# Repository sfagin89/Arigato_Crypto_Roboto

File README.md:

# Arigato the Crypto Roboto

EC544 Networking the Physical World

Spring 2022 Final Project

This project deploys a Raspberry Pi robotic car, whose movements are controlled by payments to a crypto-wallet. The robot is subscribed to a movement command topic on an AWS MQTT server. Messages are published to that topic when the robot’s crypto-wallet receives currency, Dogecoin in this case. A user scans a QR code that appears on an e-ink display sitting on top of the robot. The display is controlled by a FRDM-64F board and it interfaces with the board via a custom PCB.

Our project employs various technologies, including low-level firmware, custom PCB design, IoT communication, APIs, and crypto-currency. Ian Chadwick connected the robot with MQTT, Sara Fagin created the custom PCB for the e-ink display, and Santiago Gomez developed the e-ink firmware for the FRDM-K64F board. He is also responsible for the client application that links the robot’s crypto-wallet with its MQTT Message Broker. This report delves into the implementation of each component. Furthermore, each component discussion provides insight into the development of the respective engineer.

## Hardware
- [NXP FRDM-K64F Development Board](https://www.nxp.com/design/development-boards/freedom-development-boards/mcu-boards/freedom-development-platform-for-kinetis-k64-k63-and-k24-mcus:FRDM-K64F)
- [Waveshare’s 2.9 inch V2 e-ink display](https://www.waveshare.com/wiki/4.2inch_e-Paper_Module)
- [Adafruit Stepper + DC Motor FeatherWing motor control board](https://learn.adafruit.com/adafruit-stepper-dc-motor-featherwing)
- [RaspberryPi 3 B+](https://www.raspberrypi.com/products/raspberry-pi-3-model-b-plus/)
- [JetBot Chassis and motors](https://jetbot.org/master/index.html)
- [Custom PCB for e-Ink](https://github.com/sfagin89/Arigato_Crypto_Roboto/tree/main/PCB_files)
  - [Documentation of Full PCB Assembly](https://github.com/sfagin89/Arigato_Crypto_Roboto/tree/main/PCB_files/PCB%20Assembly)

## Software
- [Custom e-Ink Firmware](https://github.com/sfagin89/Arigato_Crypto_Roboto/tree/main/eink_firmware/development/eink_spi_firmware)
- [Robot Software](https://github.com/sfagin89/Arigato_Crypto_Roboto/tree/main/RPi)
- [Crypto App](https://github.com/sfagin89/Arigato_Crypto_Roboto/tree/main/crypto_app)

## Implementation Video
- [EC544 - Arigato Crypto Roboto](https://www.youtube.com/watch?v=zG-Wq4VXOKg)

## Final Report
- [Final Report](https://github.com/sfagin89/Arigato_Crypto_Roboto/blob/main/Final%20Project%20Report.pdf)

## Custom PCB Schematic and Board Layout

### Final PCB Schematic

### Final PCB Board Layout

### PCB Board Top Layer

### PCB Board Bottom Layer

## Functional Block Diagrams

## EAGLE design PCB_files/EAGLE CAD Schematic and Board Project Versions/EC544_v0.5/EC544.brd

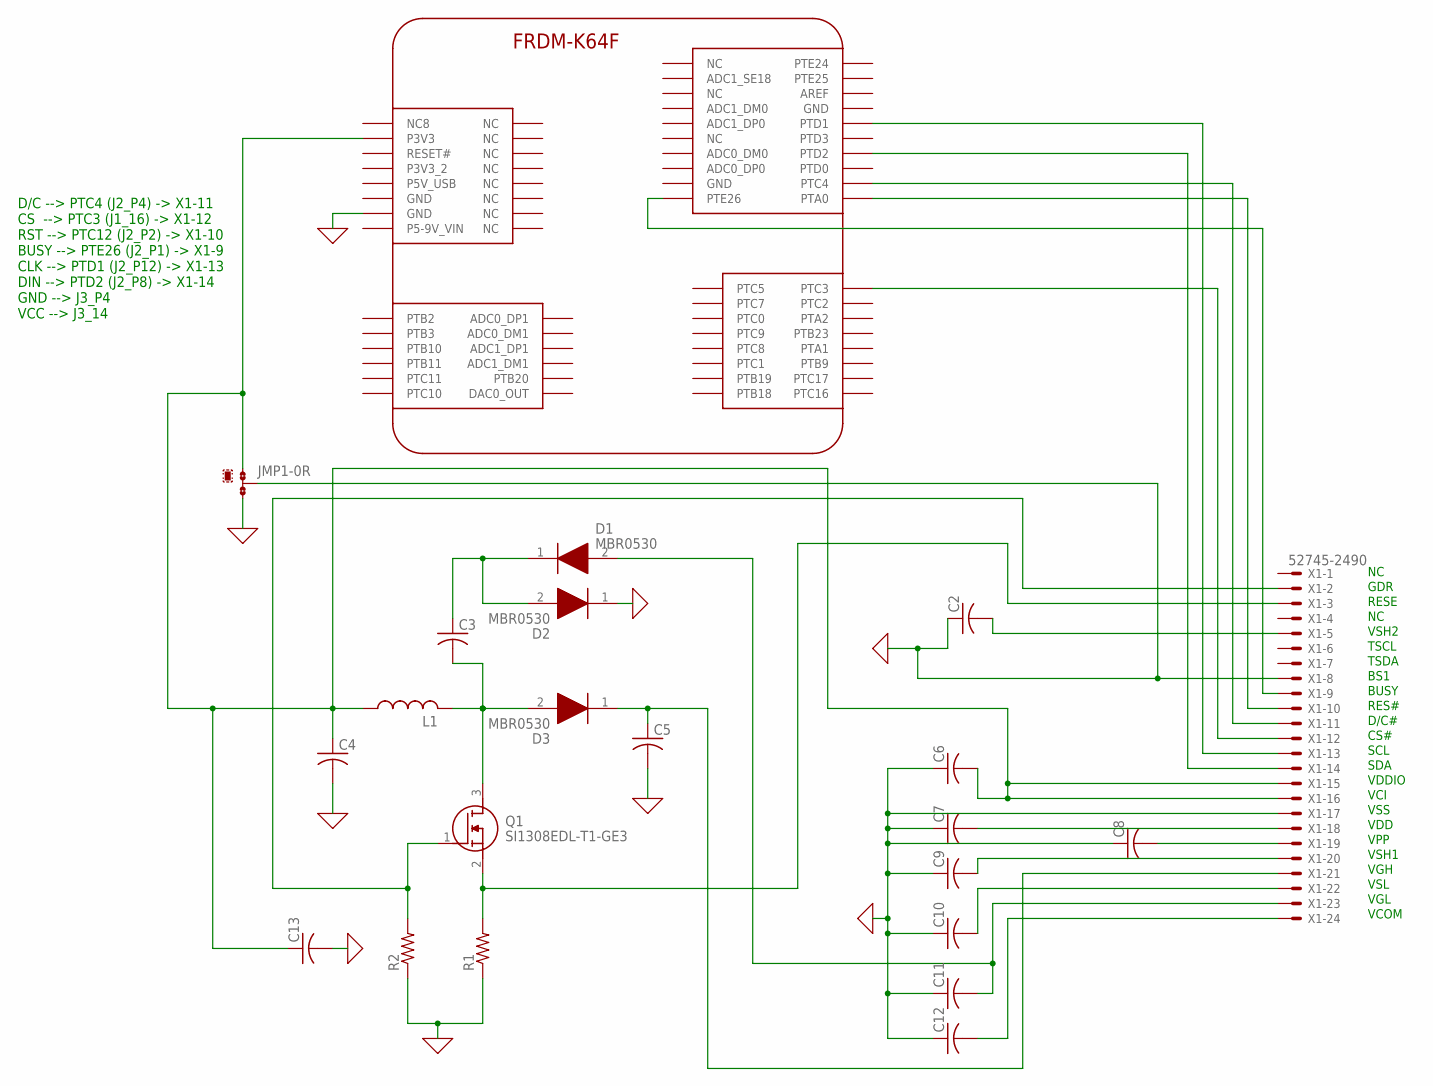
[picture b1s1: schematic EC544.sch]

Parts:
C2, C3, C4, C5, C6, C7, C8, C9, C10, C11, C12, C13: C-US025-024X044; C025-024X044
D1, D2, D3: MBR0530; SOD3716X135N
FRDM1: FRDM-K64FNORMAL; FRDM_K64F
JMP1: 0R-JUMPA; A0R-JMP
L1: L-USPIS2816; PIS2816
Q1: SI1308EDL-T1-GE3; SOT65P210X110-3N
R1, R2: R-US_0204/5; 0204/5
X1: 52745-2490

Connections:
0: C2.1, C4.2, C5.2, C6.1, C7.1, C8.1, C9.1, C10.1, C11.1, C12.1, C13.2, D2.1 (K), FRDM1.J3.14 (GND), JMP1.2, JMP1.3, R1.1, R2.1, X1.8, X1.17
unnamed: C2.2, X1.5
unnamed: C3.1, D1.1 (K), D2.2 (A)
unnamed: C7.2, X1.18
unnamed: C9.2, X1.20
unnamed: C10.2, X1.22
unnamed: C11.2, D1.2 (A), X1.23
unnamed: C12.2, X1.24
unnamed: C3.2, D3.2 (A), L1.2, Q1.3 (D)
unnamed: C5.1, D3.1 (K), X1.21
unnamed: Q1.1 (G), R2.2, X1.2
unnamed: Q1.2 (S), R1.2, X1.3
unnamed: FRDM1.J2.1 (PTE26), X1.9
unnamed: FRDM1.J2.2 (PTA0), X1.10
unnamed: FRDM1.J2.4 (PTC4), X1.11
unnamed: FRDM1.J1.16 (PTC3), X1.12
unnamed: FRDM1.J2.12 (PTD1), X1.13
unnamed: FRDM1.J2.8 (PTD2), X1.14
unnamed: C8.2, X1.19

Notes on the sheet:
D/C --> PTC4 (J2_P4) -> X1-11 CS --> PTC3 (J1_16) -> X1-12 RST --> PTC12 (J2_P2) -> X1-10 BUSY --> PTE26 (J2_P1) -> X1-9 CLK --> PTD1 (J2_P12) -> X1-13 DIN --> PTD2 (J2_P8) -> X1-14 GND --> J3_P4 VCC --> J3_14
NC GDR RESE NC VSH2 TSCL TSDA BS1 BUSY RES# D/C# CS# SCL SDA VDDIO VCI VSS VDD VPP VSH1 VGH VSL VGL VCOM

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
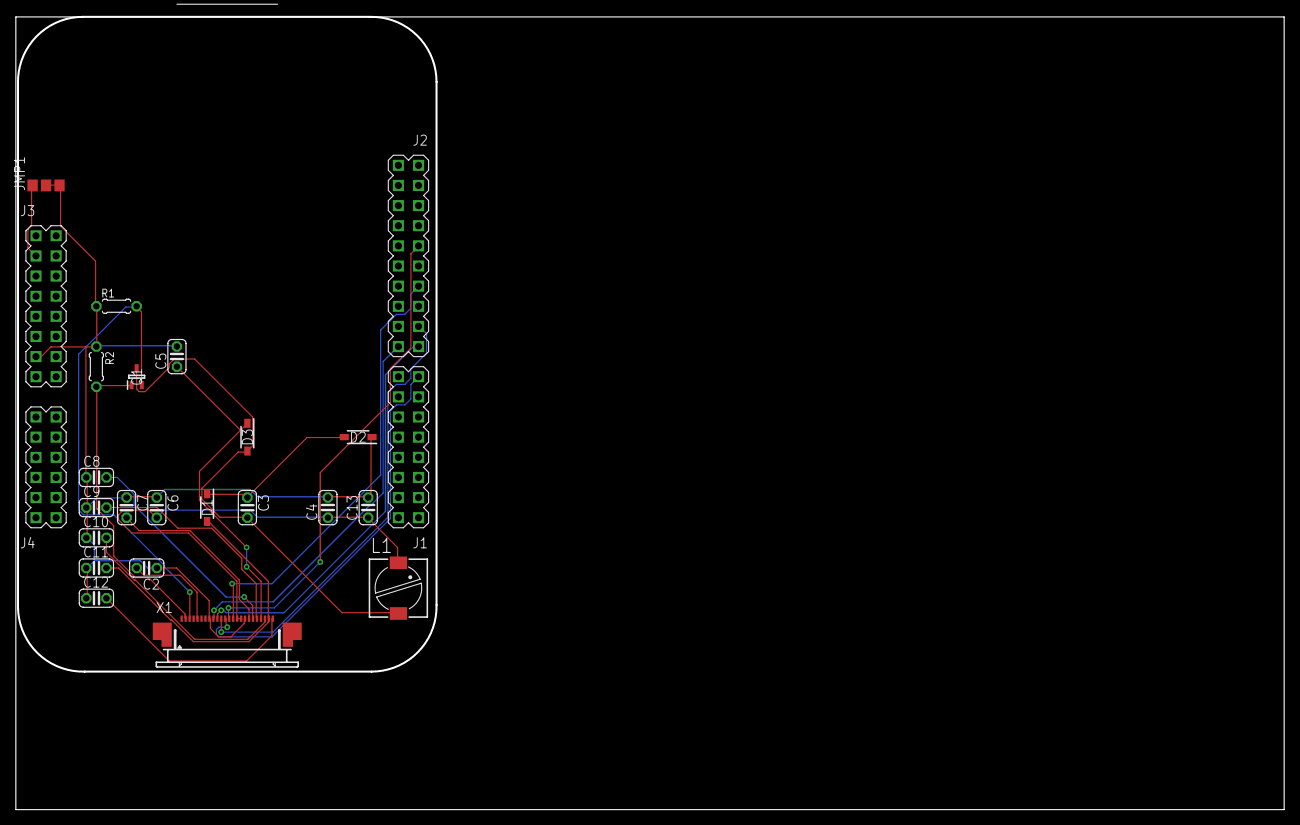
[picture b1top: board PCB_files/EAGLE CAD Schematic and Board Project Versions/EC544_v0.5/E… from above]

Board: 2 copper layers, 160.0 x 100.0 mm, 22 parts (0 on the bottom side), 21 nets.

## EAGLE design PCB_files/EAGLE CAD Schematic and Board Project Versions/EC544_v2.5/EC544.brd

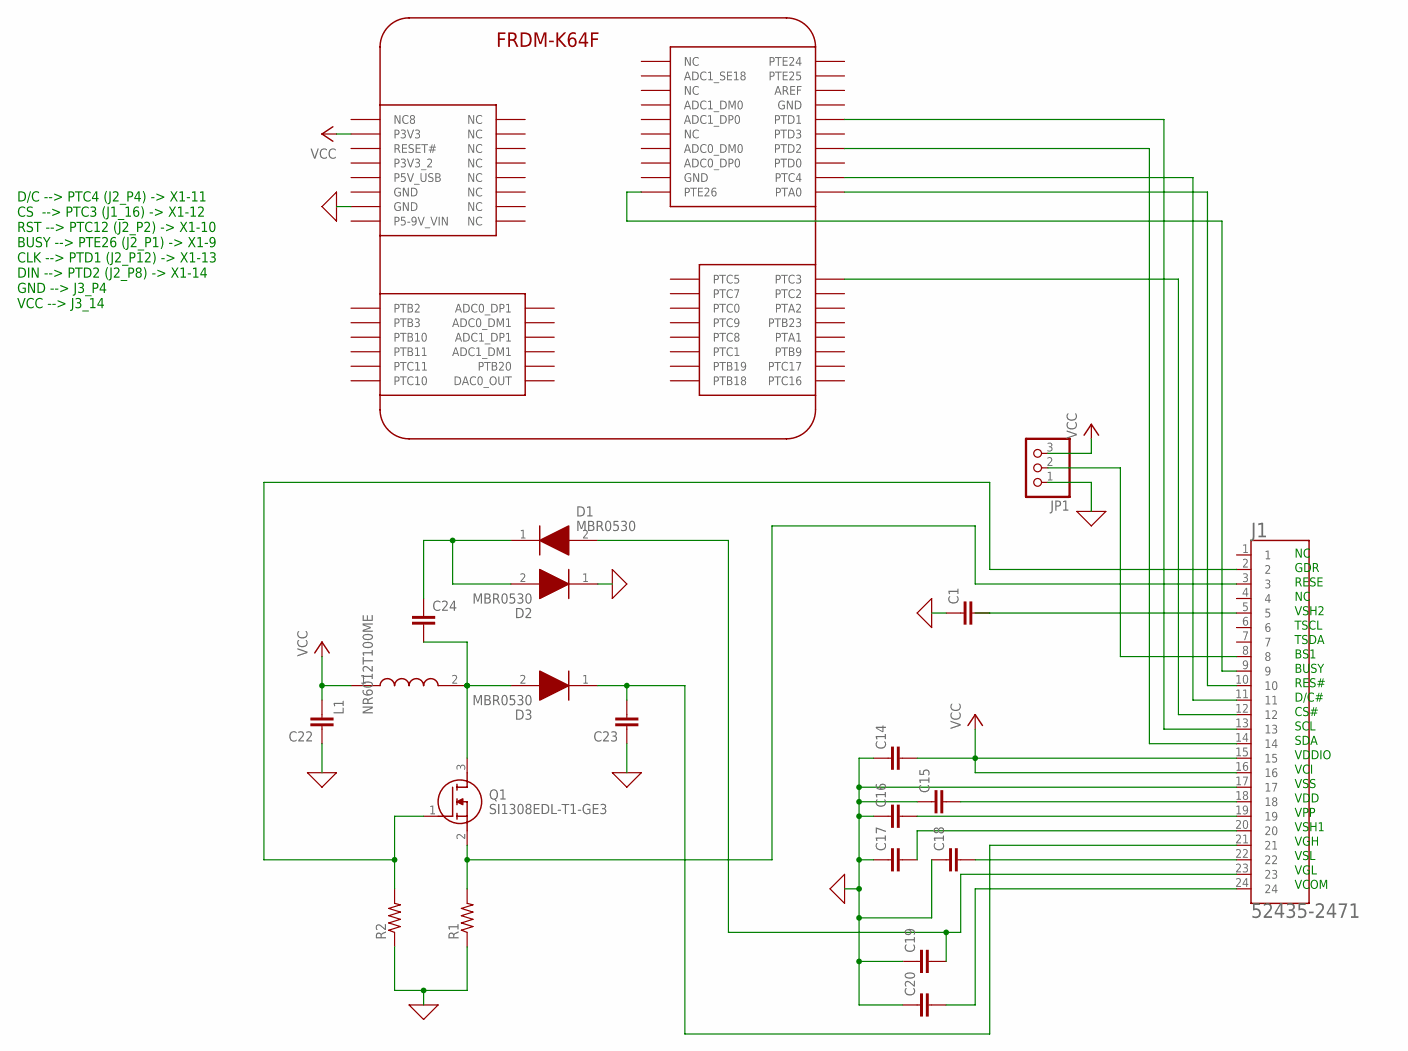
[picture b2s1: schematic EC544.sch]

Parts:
C1, C14, C15, C16, C17, C18, C19, C20, C22, C23, C24: C-EUC0805; C0805
D1, D2, D3: MBR0530; SOD3716X135N
FRDM1: FRDM-K64FNORMAL; FRDM_K64F
J1: 52435-2471; MOLEX_52435-2471
JP1: PINHD-1X3; 1X03
L1: NR6012T100ME
Q1: SI1308EDL-T1-GE3; SOT65P210X110-3N
R1, R2: R-US_0204/5; 0204/5

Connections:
0: C1.1, C14.1, C15.1, C16.1, C17.1, C18.1, C19.1, C20.1, C22.1, C23.1, D2.1 (K), FRDM1.J3.14 (GND), J1.17, JP1.1, R1.1, R2.1
unnamed: C1.2, J1.5
unnamed: J1.8, JP1.2
unnamed: C24.1, D1.1 (K), D2.2 (A)
unnamed: C15.2, J1.18
unnamed: C17.2, J1.20
unnamed: C18.2, J1.22
unnamed: C19.2, D1.2 (A), J1.23
unnamed: C20.2, J1.24
unnamed: C24.2, D3.2 (A), L1.2, Q1.3 (D)
unnamed: C23.2, D3.1 (K), J1.21
unnamed: J1.2, Q1.1 (G), R2.2
unnamed: J1.3, Q1.2 (S), R1.2
unnamed: C16.2, J1.19
unnamed: FRDM1.J2.1 (PTE26), J1.9
unnamed: FRDM1.J2.2 (PTA0), J1.10
unnamed: FRDM1.J2.4 (PTC4), J1.11
unnamed: FRDM1.J1.16 (PTC3), J1.12
unnamed: FRDM1.J2.12 (PTD1), J1.13
unnamed: FRDM1.J2.8 (PTD2), J1.14
VCC: C14.2, C22.2, FRDM1.J3.4 (P3V3), J1.15, J1.16, JP1.3, L1.1

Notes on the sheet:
D/C --> PTC4 (J2_P4) -> X1-11 CS --> PTC3 (J1_16) -> X1-12 RST --> PTC12 (J2_P2) -> X1-10 BUSY --> PTE26 (J2_P1) -> X1-9 CLK --> PTD1 (J2_P12) -> X1-13 DIN --> PTD2 (J2_P8) -> X1-14 GND --> J3_P4 VCC --> J3_14
NC GDR RESE NC VSH2 TSCL TSDA BS1 BUSY RES# D/C# CS# SCL SDA VDDIO VCI VSS VDD VPP VSH1 VGH VSL VGL VCOM

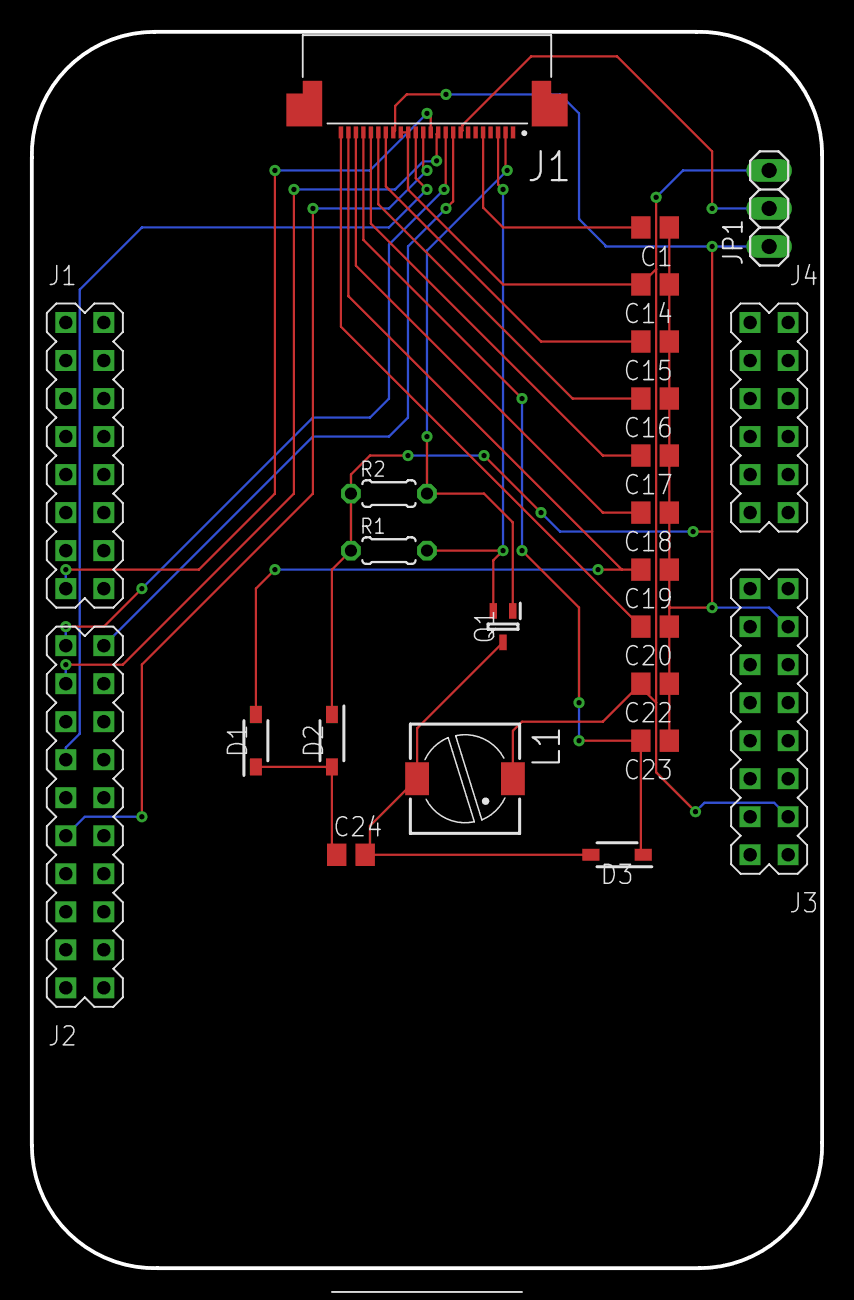
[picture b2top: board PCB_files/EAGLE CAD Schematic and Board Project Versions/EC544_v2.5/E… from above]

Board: 2 copper layers, 52.8 x 82.6 mm, 21 parts (0 on the bottom side), 21 nets.

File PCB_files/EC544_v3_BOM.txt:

Partlist exported from C:/Users/Branwen/Documents/EAGLE/projects/EC544_v3.5/EC544.sch at 5/4/2022 2:05 PM

Qty Value            Device           Package          Parts                                                Description                                                                                                       ARROW_PART_NUMBER ARROW_PRICE-STOCK                                                     AVAILABILITY DESCRIPTION                                                                                                       HEIGHT MANUFACTURER_NAME MANUFACTURER_PART_NUMBER MF    MOUSER_PART_NUMBER  MOUSER_PRICE-STOCK                                                                                                  MP         PACKAGE POPULARITY PRICE PURCHASE-URL                                                SPICEPREFIX
11                   C-EUC0805        C0805            C1, C14, C15, C16, C17, C18, C19, C20, C22, C23, C24 CAPACITOR, European symbol                                                                                                                                                                                                                                                                                                                                                                                                                                                                                                                                  88                                                                           C          
1                    FRDM-K64FNORMAL  FRDM_K64F        FRDM1                                                For creating FRDM-K64F shields                                                                                                                                                                                                                                                                                                                                                                                                                                                                                                                                                                                                                      
1                    PINHD-1X3        1X03             JP1                                                  PIN HEADER                                                                                                                                                                                                                                                                                                                                                                                                                                                                                                                                                  92                                                                                      
2                    R-US_0204/5      0204/5           R1, R2                                               RESISTOR, American symbol                                                                                                                                                                                                                                                                                                                                                                                                                                                                                                                                   18                                                                           R          
1   52435-2471       52435-2471       MOLEX_52435-2471 J1                                                   Conn FFC/FPC Connector SKT 24 POS 0.5mm Solder RA SMD Embossed T/R Check availability                                                                                                                     In Stock      24 Position FFC, FPC Connector Contacts, Top 0.020 (0.50mm) Surface Mount, Right Angle                                                                             Molex                                                                                                                                         52435-2471 None               None  https://pricing.snapeda.com/search/part/52435-2471/?ref=eda            
3   MBR0530          MBR0530          SOD3716X135N     D1, D2, D3                                           ON SEMICONDUCTOR - MBR0530 - DIODE, SCHOTTKY, 0.5A, 30V, SOD-123                                                  MBR0530           https://www.arrow.com/en/products/mbr0530/on-semiconductor?r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              ON SEMICONDUCTOR - MBR0530 - DIODE, SCHOTTKY, 0.5A, 30V, SOD-123                                                  1.35mm ON Semiconductor  MBR0530                        512-MBR0530         https://www.mouser.co.uk/ProductDetail/ON-Semiconductor-Fair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                                                                                                                  
1   NR6012T100ME     NR6012T100ME     NR6012T100ME     L1                                                   NR6012T100ME                                                                                                      NR6012T100ME      https://www.arrow.com/en/products/nr6012t100me/taiyo-yuden                         NR6012T100ME                                                                                                      1.2mm  TAIYO YUDEN       NR6012T100ME                   963-NR6012T100ME    https://www.mouser.com/Search/Refine.aspx?Keyword=963-NR6012T100ME                                                                                                                                                             
1   SI1308EDL-T1-GE3 SI1308EDL-T1-GE3 SOT65P210X110-3N Q1                                                   MOSFET N-Ch 30V 1.5A TrenchFET SC70 Vishay Si1308EDL-T1-GE3 N-channel MOSFET Transistor, 1.5 A, 30 V, 3-Pin SC-70 SI1308EDL-T1-GE3  https://www.arrow.com/en/products/si1308edl-t1-ge3/vishay?re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               MOSFET N-Ch 30V 1.5A TrenchFET SC70 Vishay Si1308EDL-T1-GE3 N-channel MOSFET Transistor, 1.5 A, 30 V, 3-Pin SC-70 1.1mm  Vishay            Si1308EDL-T1-GE3               78-SI1308EDL-T1-GE3 https://www.mouser.co.uk/ProductDetail/Vishay-Semiconductors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

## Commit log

2022-03-28 Intro/Hello World ROS packages
2022-04-02 Initial commit. Added mqttt_auth demo files, git ignore
2022-04-08 added e-ink experiment using SPI example SDK
2022-04-09 qr code now printing correctly
2022-04-11 Adding Ver1 Board Files
2022-04-12 added arigato_shadow folder with updates to include Python.h and write to shadow
2022-04-15 Updates and tests
2022-04-15 Forgot to add updates
2022-04-16 firmware is now in its own project structure
2022-04-16 now can print words onto screen
2022-04-17 Newest work completed
2022-04-22 firmware for e-ink complete
2022-04-22 updated logging metadata
2022-04-23 crypto app can access wallet balance
2022-04-24 checking dogecoin balance works
2022-04-24 adding aws mqtt
2022-04-24 can now mqtt puslish
2022-04-24 added helpful comments throughout
2022-04-24 Updated the sub/pub topic in mutual_auth_demo.c
2022-04-24 git ignore
2022-04-25 added support for three different images
2022-04-25 renamed source file to eink_spi_firmware.c
2022-04-25 readme updated
2022-04-25 added button instructions to ReadMe
2022-04-29 added update commenting DC high/low
2022-04-30 removed some comments
2022-05-01 Cleaned up comments, created final file for executable robot.c in RPi/robot/
2022-05-04 logs updated
2022-05-04 eagle project files displaying design process
2022-05-04 Updated PCB Directory
2022-05-04 Updating Board Assembly ReadMe
2022-05-04 Adjusting image size test
2022-05-04 Images added to PCB Assembly ReadMe
2022-05-04 Resized Images
2022-05-04 Updated PCB files
2022-05-04 Updated ReadMe style
2022-05-04 Adjusted Images
2022-05-04 fixing images
2022-05-04 New Images
2022-05-04 Fixed Images
2022-05-04 report added to repo
